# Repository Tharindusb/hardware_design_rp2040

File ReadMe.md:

# Hardware Design RP2040

## KiCad 3D rendering of the minimal design

### Front view:

### Back view:

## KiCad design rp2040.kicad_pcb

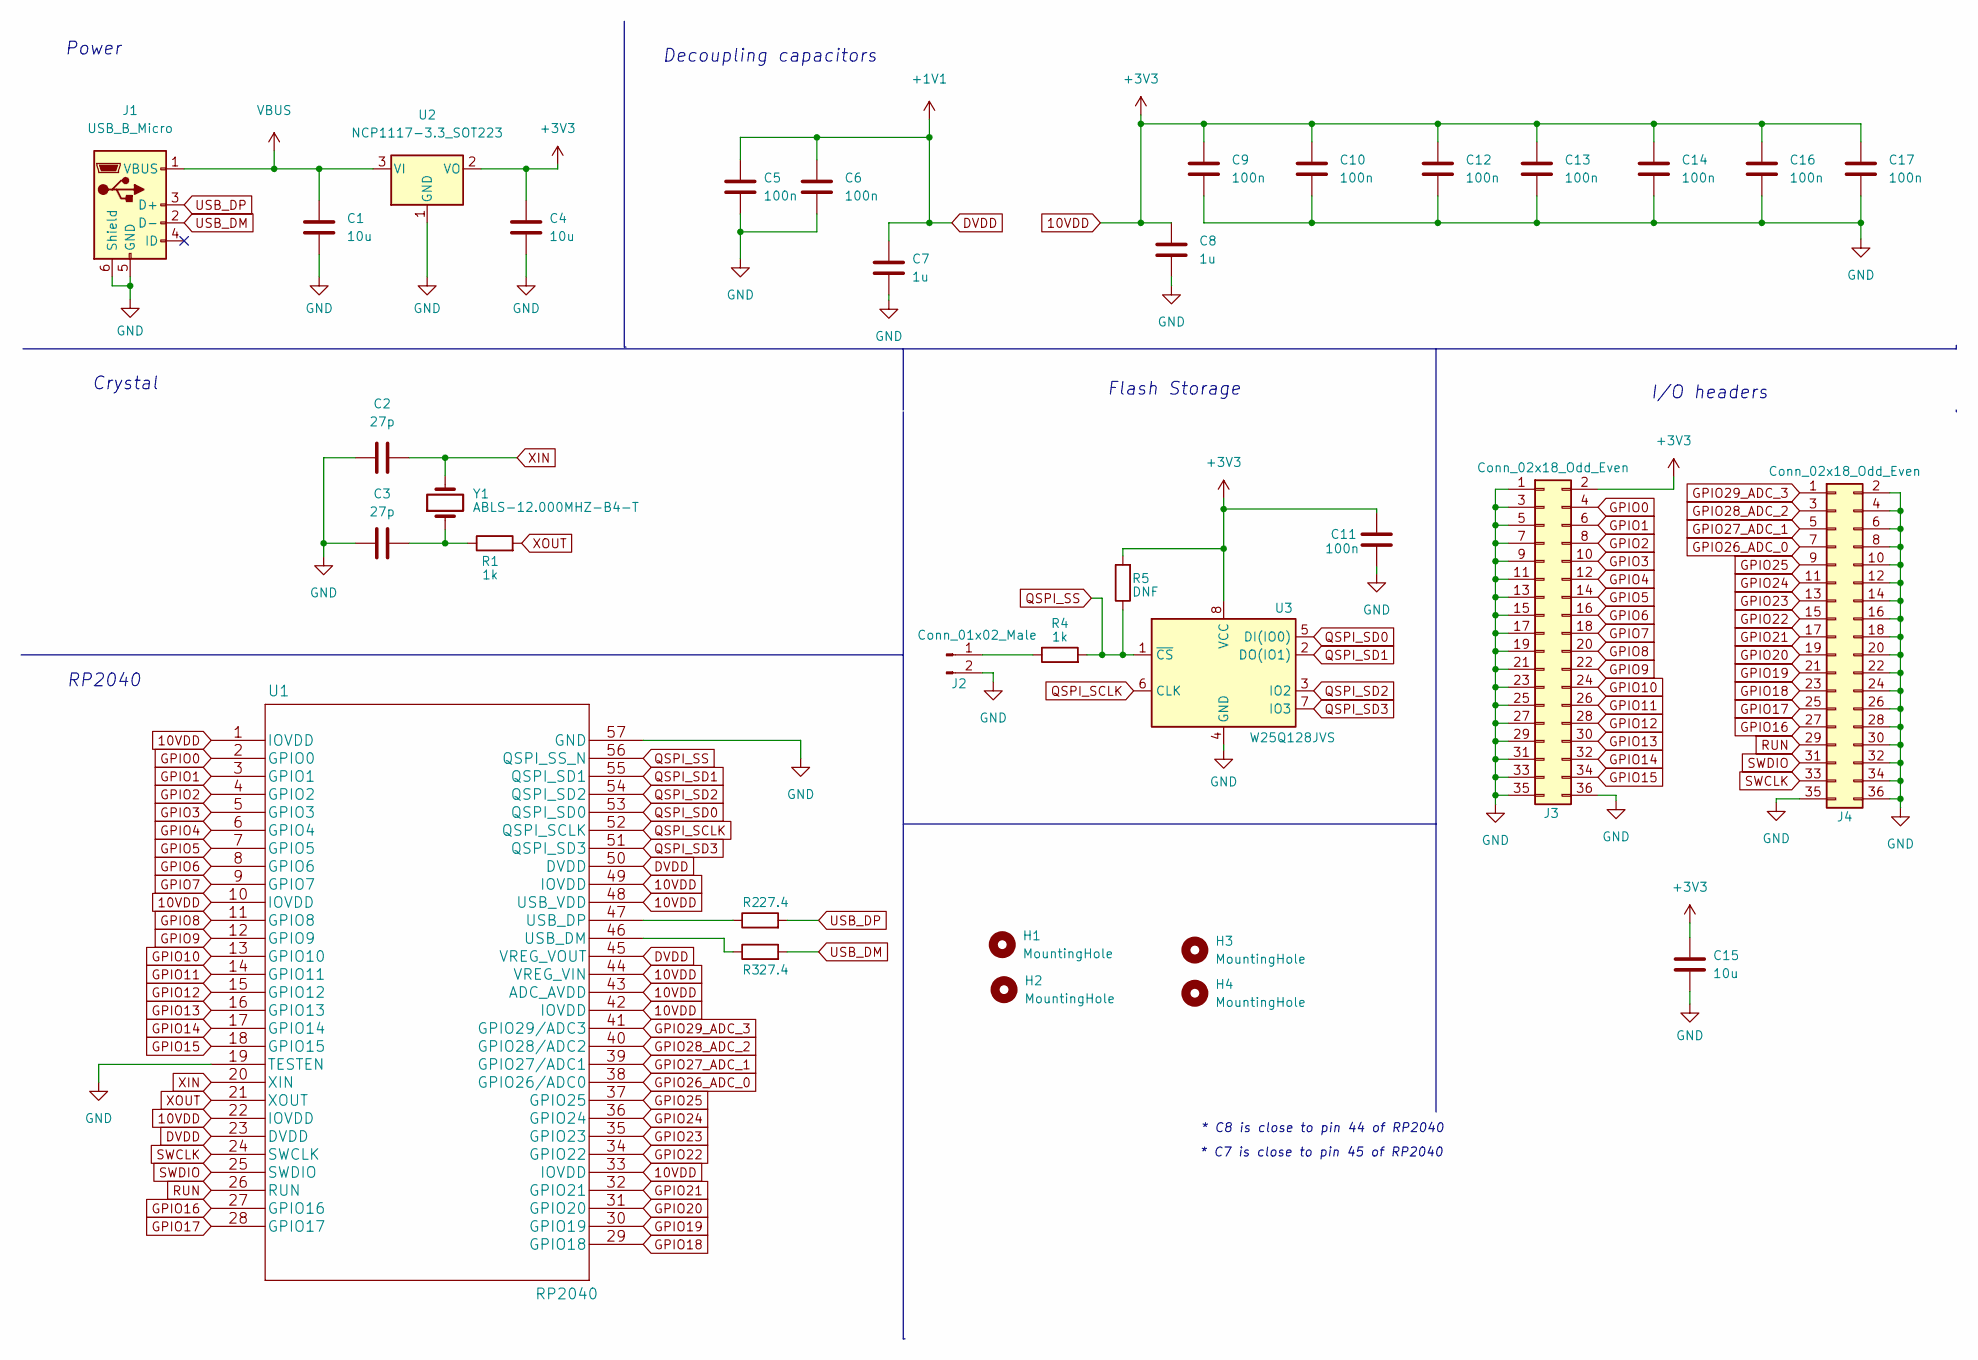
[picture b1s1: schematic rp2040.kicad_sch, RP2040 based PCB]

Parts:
C1, C4: 10u; C_0805_2012Metric_Pad1.18x1.45mm_HandSolder
C2, C3: 27p; C_0402_1005Metric_Pad0.74x0.62mm_HandSolder
C5, C6, C9, C10, C11, C12, C13, C14, C16, C17: 100n; C_0402_1005Metric_Pad0.74x0.62mm_HandSolder
C7, C8: 1u; C_0402_1005Metric_Pad0.74x0.62mm_HandSolder
C15: 10u; C_0402_1005Metric_Pad0.74x0.62mm_HandSolder
H1, H2, H3, H4: MountingHole; MountingHole_2.1mm
J1: USB_B_Micro; USB_Micro-B_GCT_USB3076-30-A
J2: Conn_01x02_Male; PinHeader_1x02_P2.00mm_Vertical
J3, J4: Conn_02x18_Odd_Even; PinHeader_2x18_P2.54mm_Vertical
R1, R4: 1k; R_0402_1005Metric_Pad0.72x0.64mm_HandSolder
R2, R3: 27.4; R_0402_1005Metric_Pad0.72x0.64mm_HandSolder
R5: DNF; R_0402_1005Metric_Pad0.72x0.64mm_HandSolder
U1: RP2040
U2: NCP1117-3.3_SOT223; SOT-223-3_TabPin2
U3: W25Q128JVS; W25Q128JVSIQ TR
Y1: ABLS-12.000MHZ-B4-T; Abracon-ABLS-12.000MHZ-B4-T-0

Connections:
10VDD: C4.1, C8.1, C9.1, C10.1, C11.1, C12.1, C13.1, C14.1, C15.1, C16.1, C17.1, J3.2, R5.2, U1.1 (IOVDD), U1.10 (IOVDD), U1.22 (IOVDD), U1.33 (IOVDD), U1.42 (IOVDD), U1.43 (ADC_AVDD), U1.44 (VREG_VIN), U1.48 (USB_VDD), U1.49 (IOVDD), U2.2 (VO), U3.8 (VCC)
DVDD: C5.1, C6.1, C7.1, U1.23 (DVDD), U1.45 (VREG_VOUT), U1.50 (DVDD)
GND: C1.2, C2.1, C3.1, C4.2, C5.2, C6.2, C7.2, C8.2, C9.2, C10.2, C11.2, C12.2, C13.2, C14.2, C15.2, C16.2, C17.2, J1.5 (GND), J1.6 (Shield), J2.2, J3.1, J3.3, J3.5, J3.7, J3.9, J3.11, J3.13, J3.15, J3.17, J3.19, J3.21, J3.23, J3.25, J3.27, J3.29, J3.31, J3.33, J3.35, J3.36, J4.2, J4.4, J4.6, J4.8, J4.10, J4.12, J4.14, J4.16, J4.18, J4.20, J4.22, J4.24, J4.26, J4.28, J4.30, J4.32, J4.34, J4.35, J4.36, U1.19 (TESTEN), U1.57 (GND), U2.1 (GND), U3.4 (GND)
GPIO0: J3.4, U1.2 (GPIO0)
GPIO1: J3.6, U1.3 (GPIO1)
GPIO2: J3.8, U1.4 (GPIO2)
GPIO3: J3.10, U1.5 (GPIO3)
GPIO4: J3.12, U1.6 (GPIO4)
GPIO5: J3.14, U1.7 (GPIO5)
GPIO6: J3.16, U1.8 (GPIO6)
GPIO7: J3.18, U1.9 (GPIO7)
GPIO8: J3.20, U1.11 (GPIO8)
GPIO9: J3.22, U1.12 (GPIO9)
GPIO10: J3.24, U1.13 (GPIO10)
GPIO11: J3.26, U1.14 (GPIO11)
GPIO12: J3.28, U1.15 (GPIO12)
GPIO13: J3.30, U1.16 (GPIO13)
GPIO14: J3.32, U1.17 (GPIO14)
GPIO15: J3.34, U1.18 (GPIO15)
GPIO16: J4.27, U1.27 (GPIO16)
GPIO17: J4.25, U1.28 (GPIO17)
GPIO18: J4.23, U1.29 (GPIO18)
GPIO19: J4.21, U1.30 (GPIO19)
GPIO20: J4.19, U1.31 (GPIO20)
GPIO21: J4.17, U1.32 (GPIO21)
GPIO22: J4.15, U1.34 (GPIO22)
GPIO23: J4.13, U1.35 (GPIO23)
GPIO24: J4.11, U1.36 (GPIO24)
GPIO25: J4.9, U1.37 (GPIO25)
GPIO26_ADC_0: J4.7, U1.38 (GPIO26/ADC0)
GPIO27_ADC_1: J4.5, U1.39 (GPIO27/ADC1)
GPIO28_ADC_2: J4.3, U1.40 (GPIO28/ADC2)
GPIO29_ADC_3: J4.1, U1.41 (GPIO29/ADC3)
unnamed: C3.2, R1.1, Y1.1
unnamed: J2.1, R4.1
unnamed: R2.1, U1.47 (USB_DP)
unnamed: R3.1, U1.46 (USB_DM)
QSPI_SCLK: U1.52 (QSPI_SCLK), U3.6 (CLK)
QSPI_SD0: U1.53 (QSPI_SD0), U3.5 (DI(IO0))
QSPI_SD1: U1.55 (QSPI_SD1), U3.2 (DO(IO1))
QSPI_SD2: U1.54 (QSPI_SD2), U3.3 (IO2)
QSPI_SD3: U1.51 (QSPI_SD3), U3.7 (IO3)
QSPI_SS: R4.2, R5.1, U1.56 (QSPI_SS_N), U3.1 (~CS)
RUN: J4.29, U1.26 (RUN)
SWCLK: J4.33, U1.24 (SWCLK)
SWDIO: J4.31, U1.25 (SWDIO)
USB_DM: J1.2 (D-), R3.2
USB_DP: J1.3 (D+), R2.2
VBUS: C1.1, J1.1 (VBUS), U2.3 (VI)
XIN: C2.2, U1.20 (XIN), Y1.2
XOUT: R1.2, U1.21 (XOUT)

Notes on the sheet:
* C7 is close to pin 45 of RP2040
Flash Storage
I/O headers
RP2040
Power
Decoupling capacitors
Crystal
* C8 is close to pin 44 of RP2040

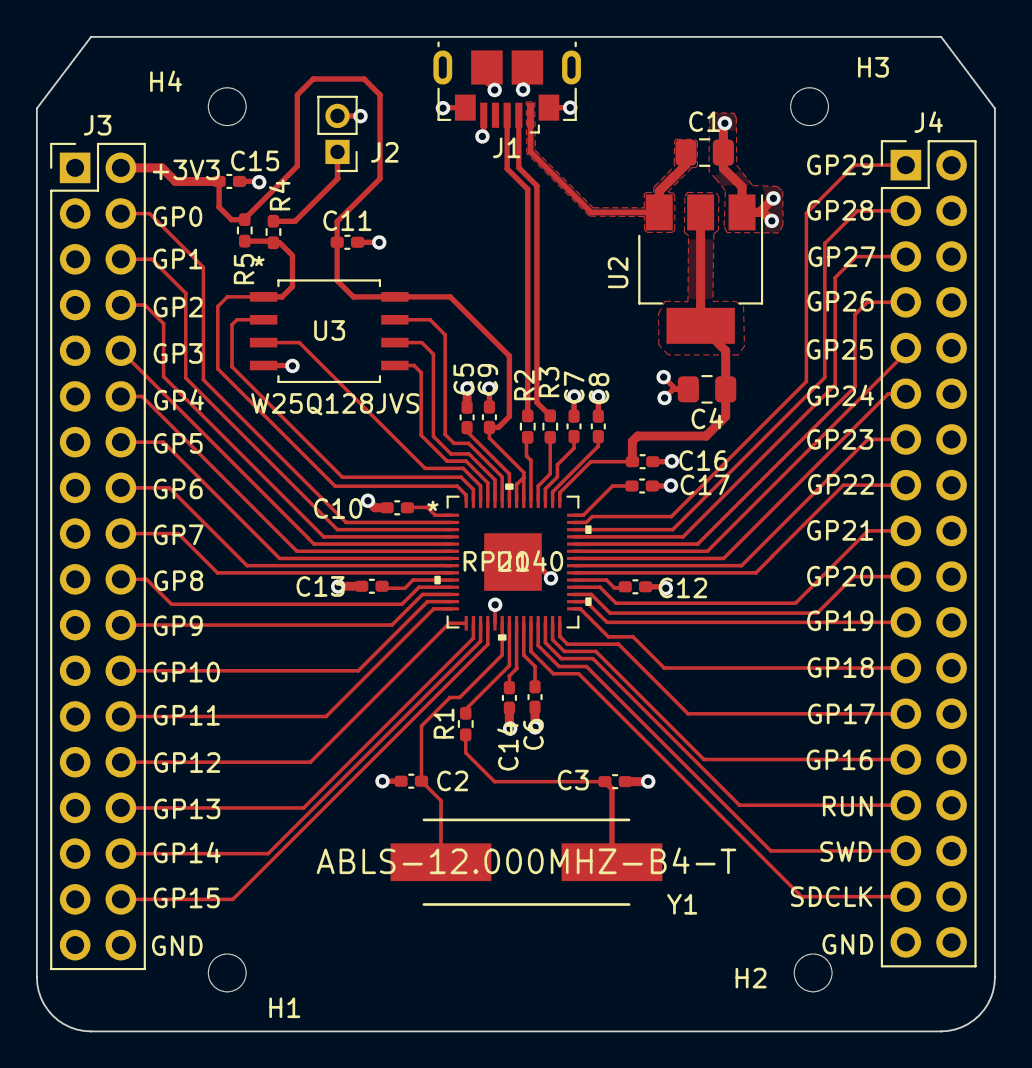
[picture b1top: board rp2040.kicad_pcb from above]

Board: 2 copper layers, 53.2 x 55.3 mm, 34 parts (0 on the bottom side), 51 nets.

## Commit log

2022-07-19 rp2040 hardware design
2022-07-19 added img
2022-07-19 bug fixed
2022-07-19 fix img size

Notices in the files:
parts and their libraries:
Copyright 2021 Accelerated Designs. All rights reserved.
